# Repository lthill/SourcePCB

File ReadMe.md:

# Source Turbo Control PCB

## PN 203, Rev A1

This is a new version of the Source Turbo control PCB SRC_REV_Q

### Major changes
1. Replacement of the MXP5100DP with a 0-100Kpa absolute pressure sensor, 3.3V
2. Depopulated RN4020 BLE Module
3. Additional test point pads for use with Keystone 5010
4. New analog signal chains forced by sensor change
5. PCB layout changes driven by the sensor
6. Additional of test points

Output signal chain is the same from the Rev_Q Board.
The orginal, difficult to read schematic, remains the same. :-(

Removal of the BLE frees the hardware UART and the bulk of the processor resources.
Processing time was already generous *with the removal of blocking code* even with BLE 
Bi-Directional terminal access may be a very useful development option.

### Software Requirements
1. Removal of the BLE will require significant software changes
2. Patch for absolute pressure sensor

## Implementaion
Removal of the BLE will require patches or a re-write.
The absolute pressure sensor should be an object with private variables and allow for different pressure ranges.
Suggest looking are ratiometric sensor for characterizaton. https://github.com/lthill/ratiometric-sensor

## TODO
- [ ] Basic verification of the new hardware
- [ ] Test pressure sensor analog signal chain
- [ ] Test thermistor signal chain
- [ ] Sensor is unvalidated for use with with ethanol
- [ ] Softwre patch to remove BLE code
- [ ] Software patch for the new sensor

## Demo Sensors
- XGZP6858A15115KPAL0, 15-115kPa, 5V
- XGZP6858A15115KPAL033, 15-115kPa, 3.3V

Note the different pressure ranges

## Fallback Options
1. If validation doesn't pass use MPXH6115AC6U
2. Use OEM, CFSensor XGZP6869A100KPGL033, HBP1311A, HBP1501D, Senoch GZP6858A15115KPA50KL0

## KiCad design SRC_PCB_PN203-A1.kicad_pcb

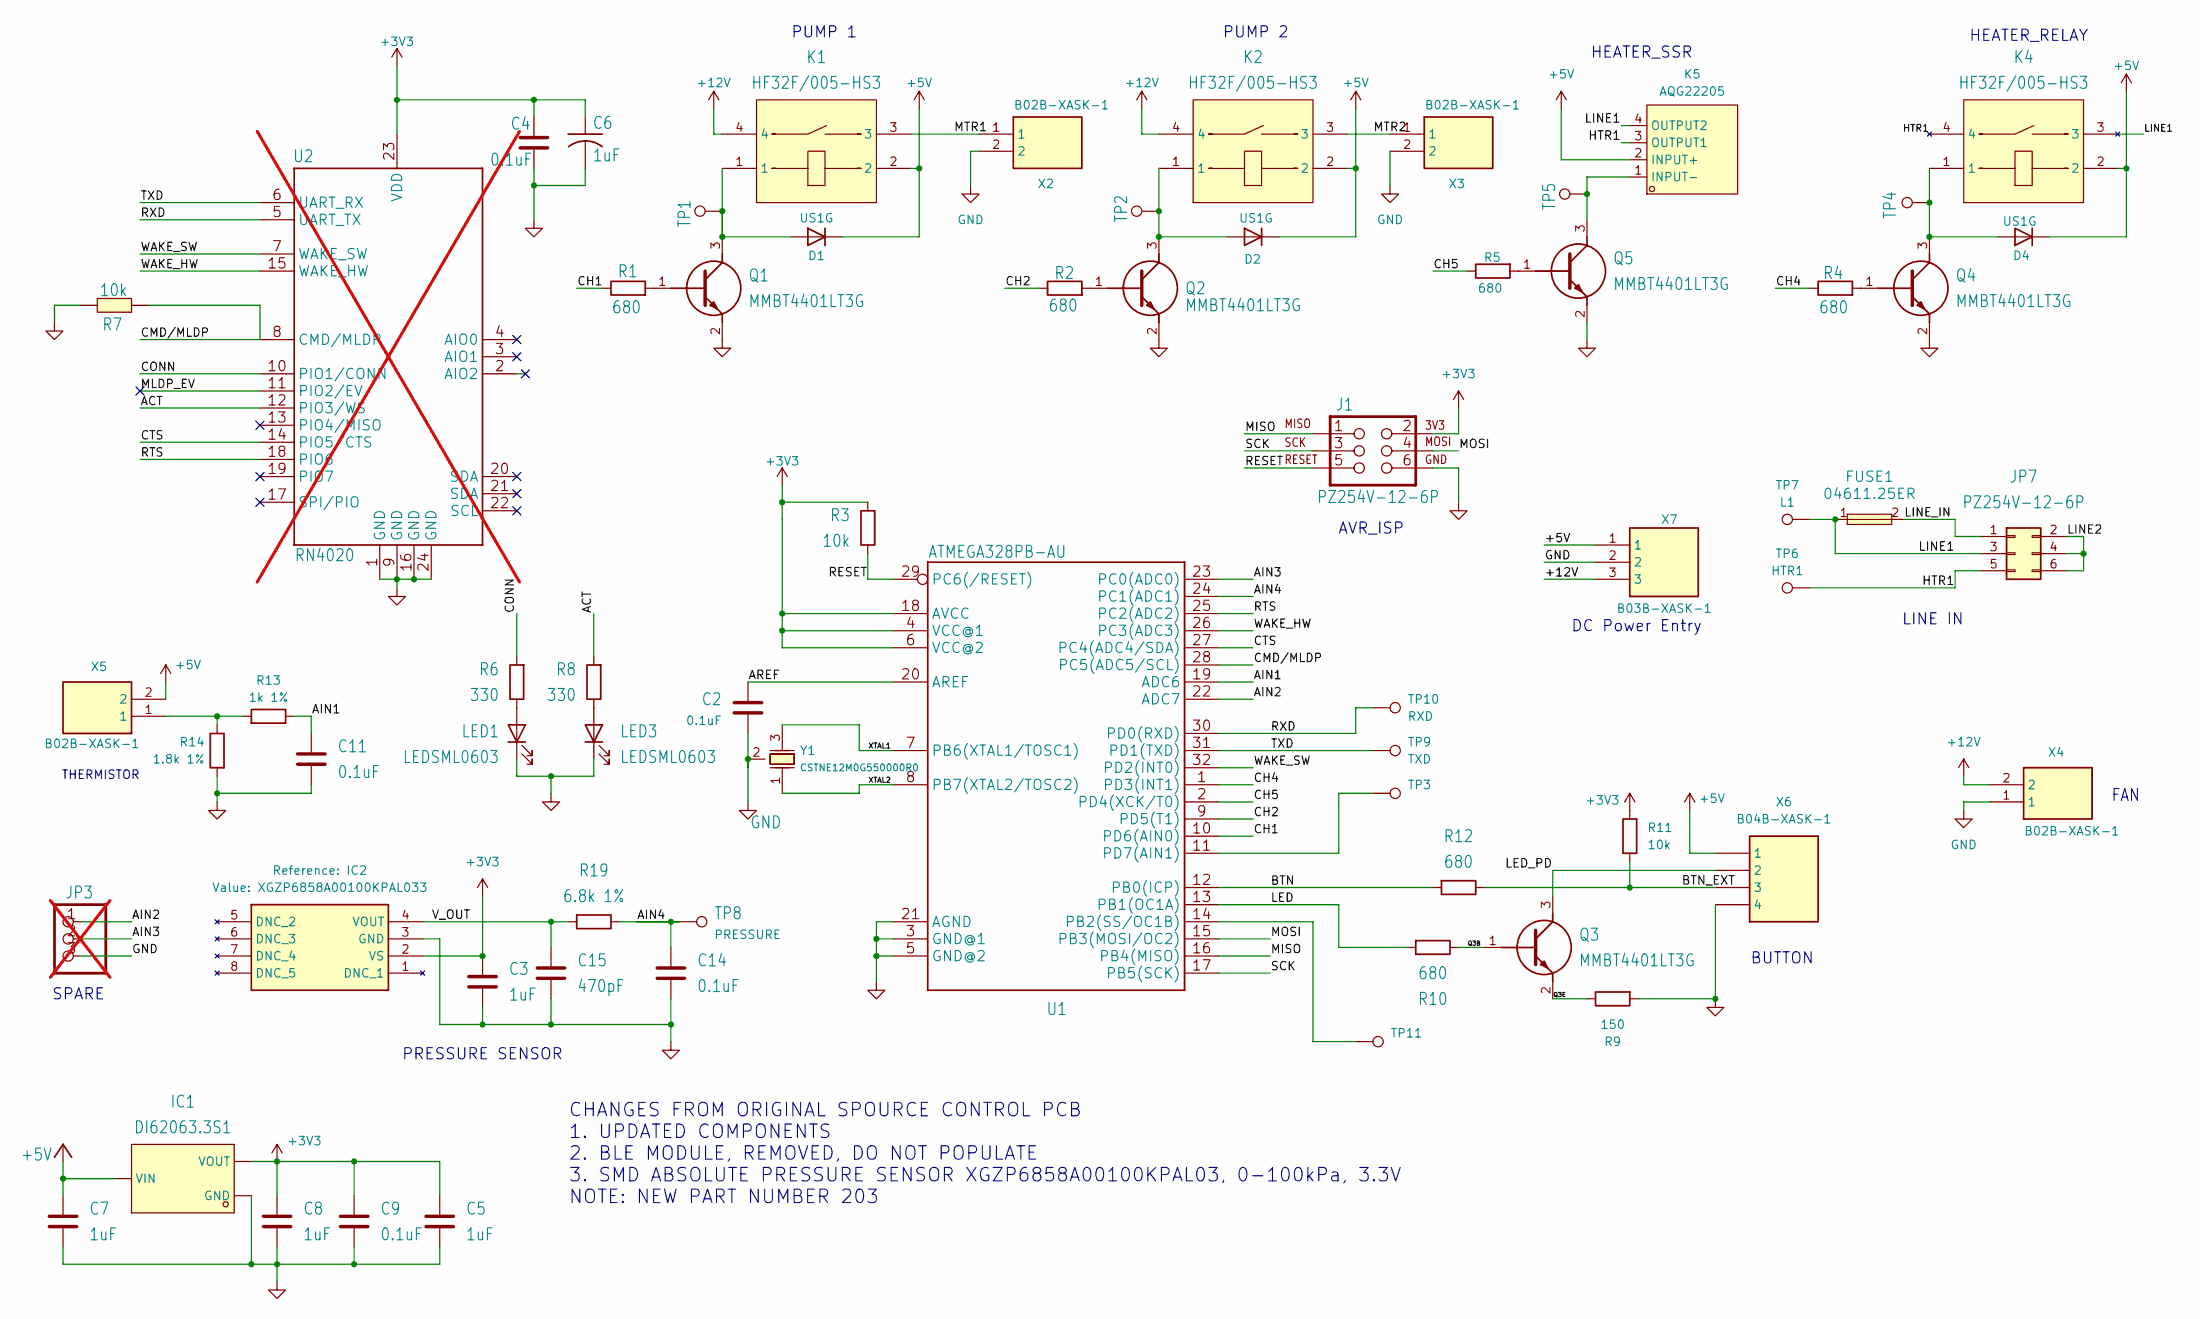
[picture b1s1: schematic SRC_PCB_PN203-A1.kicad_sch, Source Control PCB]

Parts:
C2, C4, C9, C11, C14: 0.1uF; C_0603_1608Metric; Manufacturer_Part_Number CL10B104KB8NNNC
C3, C5, C6, C7, C8: 1uF; C_0603_1608Metric; Manufacturer_Part_Number CL10A105KB8NNNC
C15: 470pF; C_0603_1608Metric; Manufacturer_Part_Number CC0603KRX7R9BB471
D1, D2, D4: US1G; D_SMA; Manufacturer_Part_Number US1G
FUSE1: 04611.25ER; FUSE-SMD_L10.1-W3.1; Manufacturer_Part_Number 04611.25ER; LCSC Part C99554
IC1: DI62063.3S1; SOT-23-3; Manufacturer_Part_Number DI62063.3S1
IC2: XGZP6858A00100KPAL033; MPXH6115AC6U; Manufacturer_Part_Number XGZP6858A00100KPAL033
J1: PZ254V-12-6P; PinHeader_2x03_P2.54mm_Vertical; Manufacturer_Part_Number PZ254V-12-6P
JP3: PINHD-1X3; PinHeader_1x03_P1.00mm_Vertical; not fitted
JP7: PZ254V-12-6P; PinHeader_2x03_P2.54mm_Vertical; Manufacturer_Part_Number PZ254V-12-6P
K1, K2, K4: HF32F/005-HS3; RELAY-TH_HF32F-X-HXXXX-XXX; Manufacturer_Part_Number HF32F/005-HS3
K5: AQG22205; RELAYS-TH_AQG22205; Manufacturer_Part_Number AQG22205; LCSC Part C329304
LED1, LED3: LEDSML0603; LED_0603_1608Metric; Manufacturer_Part_Number NCD0603R1; LCSC Part C124000
Q1, Q2, Q3, Q4, Q5: MMBT4401LT3G; SOT96P237X111-3N; Manufacturer_Part_Number MMBT4401LT3G
R1, R2, R4, R5, R10, R12: 680; R_0603_1608Metric; Manufacturer_Part_Number RC0603JR-071KL
R3, R11: 10k; R_0603_1608Metric; Manufacturer_Part_Number RC0603JR-0710KL
R6, R8: 330; R_0603_1608Metric; Manufacturer_Part_Number RC0603JR-07330RL
R7: 10k; R_0603_1608Metric; Manufacturer_Part_Number RC0603JR-0710KL; LCSC Part C98220
R9: 150; R_0603_1608Metric; Manufacturer_Part_Number RC0603JR-07150RL
R13: 1k 1%; R_1206_3216Metric_Pad1.30x1.75mm_HandSolder; Manufacturer_Part_Number RC1206FR-071KL
R14: 1.8k 1%; R_1206_3216Metric_Pad1.30x1.75mm_HandSolder; Manufacturer_Part_Number RC1206FR-071K8L
R19: 6.8k 1%; R_1206_3216Metric_Pad1.30x1.75mm_HandSolder; Manufacturer_Part_Number RC1206FR-076K8L
TP1: K1; TestPoint_Pad_D1.0mm
TP2: K2; TestPoint_Pad_D1.0mm
TP3: PIN11; TestPoint_Keystone_5010-5014_Multipurpose
TP4: K4; TestPoint_Pad_D1.0mm
TP5: K5; TestPoint_Pad_D1.0mm
TP6: HTR1; SolderWire-0.75sqmm_1x01_D1.25mm_OD3.5mm
TP7: L1; SolderWire-0.75sqmm_1x01_D1.25mm_OD3.5mm
TP8: PRESSURE; TestPoint_Pad_D1.0mm
TP9: TXD; TestPoint_Keystone_5010-5014_Multipurpose
TP10: RXD; TestPoint_Keystone_5010-5014_Multipurpose
TP11: PIN14; TestPoint_Keystone_5010-5014_Multipurpose
U1: ATMEGA328PB-AU; TQFP-32_7x7mm_P0.8mm; Manufacturer_Part_Number ATMEGA328PB-AU
U2: RN4020; WIRELM-SMD_RN4020-V-RM; Manufacturer_Part_Number RN4020-V/RM; not fitted
X2, X3, X4, X5: B02B-XASK-1; JST_XA_B02B-XASK-1_1x02_P2.50mm_Vertical; Manufacturer_Part_Number B02B-XASK-1
X6: B04B-XASK-1; JST_XA_B04B-XASK-1_1x04_P2.50mm_Vertical; Manufacturer_Part_Number B04B-XASK-1
X7: B03B-XASK-1; JST_XA_B03B-XASK-1_1x03_P2.50mm_Vertical; Manufacturer_Part_Number B03B-XASK-1
Y1: CSTNE12M0G550000R0; Resonator_SMD_Murata_CSTxExxV-3Pin_3.0x1.1mm; Manufacturer_Part_Number CSTNE12M0G550000R0

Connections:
+3V3: C3.1, C4.1, C5.1, C6.1, C8.1, C9.1, IC1.2 (VOUT), IC2.2 (VS), J1.2, R3.2, R11.2, U1.4 (VCC@1), U1.6 (VCC@2), U1.18 (AVCC), U2.23 (VDD)
+5V: C7.1, D1.1 (K), D2.1 (K), D4.1 (K), IC1.3 (VIN), K1.2, K2.2, K4.2, K5.2 (INPUT+), X5.2, X6.1, X7.1
+12V: K1.4, K2.4, X4.2, X7.3
/ACT: R8.2, U2.12 (PIO3/WS)
/AIN1: C11.1, R13.1, U1.19 (ADC6)
/AIN2: JP3.1, U1.22 (ADC7)
/AIN3: JP3.2, U1.23 (PC0(ADC0))
/AIN4: C14.1, R19.1, TP8.1 (1_1), U1.24 (PC1(ADC1))
/AREF: C2.1, U1.20 (AREF)
/BTN: R12.2, U1.12 (PB0(ICP))
/BTN_EXT: R11.1, R12.1, X6.3
/CH1: R1.1, U1.10 (PD6(AIN0))
/CH2: R2.1, U1.9 (PD5(T1))
/CH4: R4.1, U1.1 (PD3(INT1))
/CH5: R5.1, U1.2 (PD4(XCK/T0))
/CMD/MLDP: R7.1, U1.28 (PC5(ADC5/SCL)), U2.8 (CMD/MLDP)
/CONN: R6.2, U2.10 (PIO1/CONN)
/CTS: U1.27 (PC4(ADC4/SDA)), U2.14 (PIO5/CTS)
/HTR1: JP7.5, K4.4, K5.3 (OUTPUT1), TP6.1 (1_1)
/LED: R10.2, U1.13 (PB1(OC1A))
/LED_PD: Q3.3 (C), X6.2
/LINE1: FUSE1.1, JP7.3, K4.3, K5.4 (OUTPUT2), TP7.1 (1_1)
/LINE2: JP7.2, JP7.4, JP7.6
/LINE_IN: FUSE1.2, JP7.1
/MISO: J1.1, U1.16 (PB4(MISO))
/MLDP_EV: U2.11 (PIO2/EV)
/MOSI: J1.4, U1.15 (PB3(MOSI/OC2))
/MTR1: K1.3, X2.1
/MTR2: K2.3, X3.1
/Q3B: Q3.1 (B), R10.1
/Q3E: Q3.2 (E), R9.1
/RESET: J1.5, R3.1, U1.29 (PC6(/RESET))
/RTS: U1.25 (PC2(ADC2)), U2.18 (PIO6)
/RXD: TP10.1 (1_1), U1.30 (PD0(RXD)), U2.5 (UART_TX)
/SCK: J1.3, U1.17 (PB5(SCK))
/TXD: TP9.1 (1_1), U1.31 (PD1(TXD)), U2.6 (UART_RX)
/V_OUT: C15.1, IC2.4 (VOUT), R19.2
/WAKE_HW: U1.26 (PC3(ADC3)), U2.15 (WAKE_HW)
/WAKE_SW: U1.32 (PD2(INT0)), U2.7 (WAKE_SW)
/XTAL1: U1.7 (PB6(XTAL1/TOSC1)), Y1.3 (OUTPUT)
/XTAL2: U1.8 (PB7(XTAL2/TOSC2)), Y1.1 (INPUT)
GND: C2.2, C3.2, C4.2, C5.2, C6.2, C7.2, C8.2, C9.2, C11.2, C14.2, C15.2, IC1.1 (GND), IC2.3 (GND), J1.6, JP3.3, LED1.1 (K), LED3.1 (K), Q1.2 (E), Q2.2 (E), Q4.2 (E), Q5.2 (E), R7.2, R9.2, R14.2, U1.3 (GND@1), U1.5 (GND@2), U1.21 (AGND), U2.1 (GND), U2.9 (GND), U2.16 (GND), U2.24 (GND), X2.2, X3.2, X4.1, X6.4, X7.2, Y1.2 (GND)
unnamed: D1.2 (A), K1.1, Q1.3 (C), TP1.1 (1_1)
unnamed: D2.2 (A), K2.1, Q2.3 (C), TP2.1 (1_1)
unnamed: D4.2 (A), K4.1, Q4.3 (C), TP4.1 (1_1)
unnamed: K5.1 (INPUT-), Q5.3 (C), TP5.1 (1_1)
unnamed: LED1.2 (A), R6.1
unnamed: LED3.2 (A), R8.1
unnamed: Q1.1 (B), R1.2
unnamed: Q2.1 (B), R2.2
unnamed: Q4.1 (B), R4.2
unnamed: Q5.1 (B), R5.2
unnamed: R13.2, R14.1, X5.1
unnamed: TP11.1 (1_1), U1.14 (PB2(SS/OC1B))
unnamed: TP3.1 (1_1), U1.11 (PD7(AIN1))

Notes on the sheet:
THERMISTOR
CHANGES FROM ORIGINAL SPOURCE CONTROL PCB 1. UPDATED COMPONENTS 2. BLE MODULE, REMOVED, DO NOT POPULATE 3. SMD ABSOLUTE PRESSURE SENSOR XGZP6858A00100KPAL03, 0-100kPa, 3.3V NOTE: NEW PART NUMBER 203
DC Power Entry
PUMP 1
HEATER_SSR
SPARE
AVR_ISP
LINE IN
PUMP 2
BUTTON
FAN
PRESSURE SENSOR
HEATER_RELAY

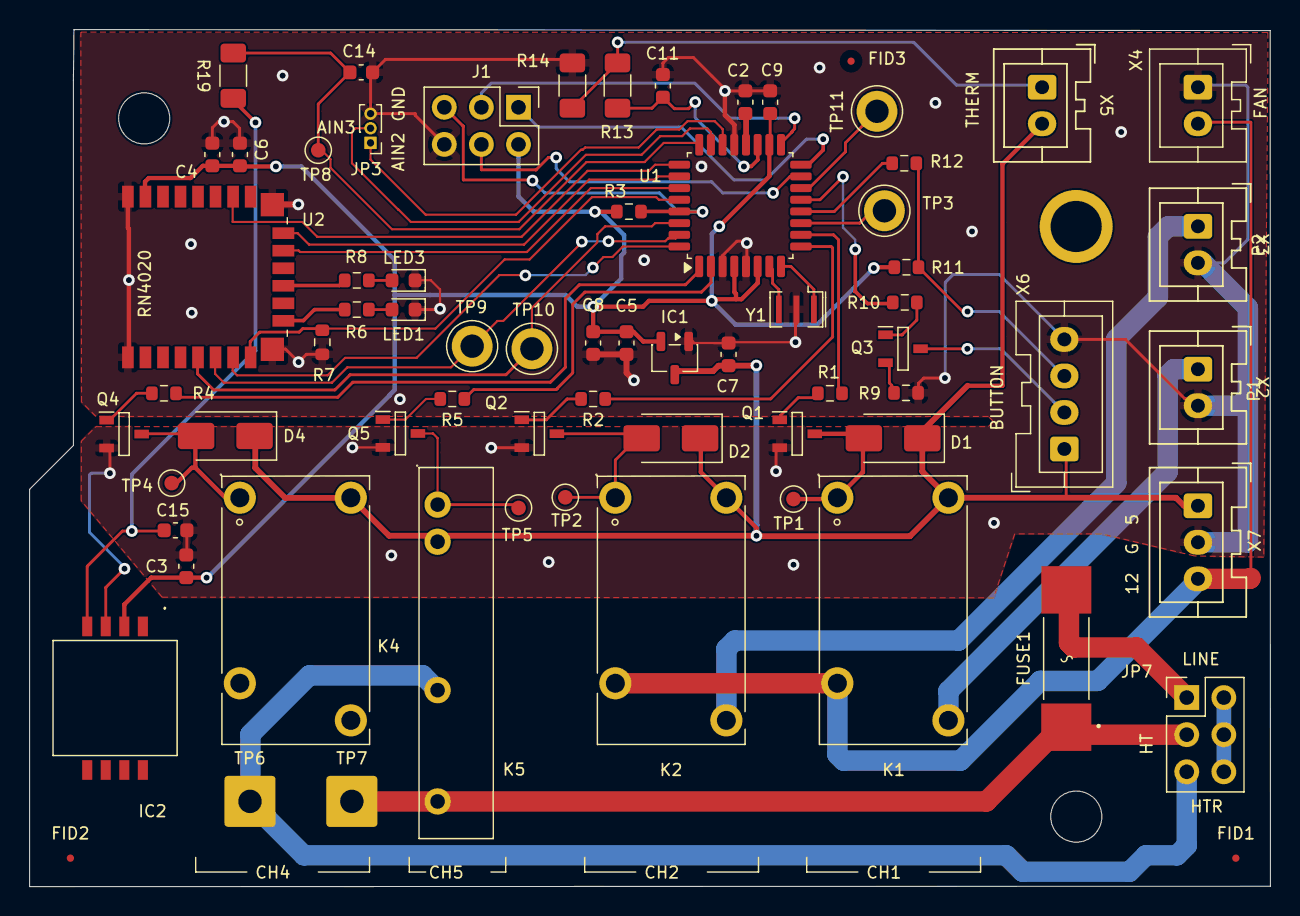
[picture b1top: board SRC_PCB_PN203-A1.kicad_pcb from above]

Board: 2 copper layers, 84.9 x 58.7 mm, 72 parts (0 on the bottom side), 54 nets.

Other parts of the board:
FID1, FID2, FID3: Fiducial_0.5mm_Mask1.5mm
H1: MountingHole_3.5mm_Pad
H2, H3: MountingHole_3.5mm
